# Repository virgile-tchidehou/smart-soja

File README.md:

<div align="center">

# 🌱 SMART-SOJA

### An Autonomous IoT-Based Mobile Soybean Pre-processing System

**[Documentation](#-documentation) · [Architecture](#️-system-architecture) · [Hardware](#️-hardware-overview) · [Roadmap](#-project-roadmap)**

</div>

---

SMART-SOJA is an academic engineering project co-developed by **Elisa Christelle LOKO** and **Dodji Virgile TCHIDEHOU**. It explores a mobile and connected soybean pre-processing unit designed to improve post-harvest handling in rural environments.

The prototype combines embedded systems, industrial automation, IoT technologies and an off-grid solar/battery architecture. At its current stage, the project is a **functional proof of concept**: the main sensing, actuation, drying and IoT subsystems have been validated individually or in partial integration, while full-cycle validation under a real 2–5 kg load and final HX711 weighing integration remain future work.

<div align="center">

</div>

---

## 📖 Table of Contents

- Overview
- The Problem
- Objectives
- Key Features
- System Architecture
- Hardware Overview
- Software Architecture
- Technology Stack
- Repository Structure
- Documentation
- Roadmap
- Future Improvements
- Project Team
- License

---

# 📌 Overview

Soybean production is rapidly increasing across Africa, particularly in Benin. However, post-harvest losses caused by inadequate cleaning, excessive moisture and poor traceability continue to reduce product quality and market value.

SMART-SOJA addresses these challenges by providing a mobile cyber-physical system capable of:

- Cleaning soybean grains through a vibrating sieve mechanism
- Measuring grain moisture at two points
- Controlling an active drying subsystem
- Supporting final batch weighing through an HX711-based subsystem *(final integration pending)*
- Recording production data locally
- Synchronizing traceability data through MQTT

The project integrates mechanical engineering, embedded electronics, industrial automation and cloud connectivity into a single modular platform.

---

# ❗ The Problem

Smallholder farmers often face several challenges:

- High post-harvest losses
- Non-uniform drying
- Manual quality control
- Lack of digital traceability
- Limited access to electricity

SMART-SOJA was designed to provide an affordable and intelligent solution adapted to rural environments.

---

# 🎯 Objectives

The project aims to:

- automate soybean pre-processing;
- improve grain quality before storage;
- reduce moisture-related losses;
- provide digital traceability;
- support off-grid operation through a solar/battery power architecture;
- support smart agriculture initiatives.

---

# ✨ Key Features

- 🌱 Mobile modular platform
- 📡 IoT connectivity using MQTT
- ⚙️ Embedded control with ESP32
- ☀️ Solar/battery off-grid power architecture
- 💧 Dual moisture sensing
- 🔥 Active drying control
- ⚖️ HX711-based weighing subsystem *(final integration pending)*
- 💾 Offline data logging (MicroSD)
- ☁️ Cloud synchronization
- 📊 Real-time monitoring
- 🧠 FreeRTOS multitasking architecture
- 🔄 GRAFCET-based sequential control

---

# 🏗️ System Architecture

SMART-SOJA is composed of six major subsystems:

## Mechanical System

- Modular chassis
- Cleaning mechanism
- Drying chamber
- Weighing module
- Mobile structure

## Embedded Electronics

- ESP32 microcontroller
- Sensors
- Power electronics
- Human-Machine Interface

## Energy System

- Solar panel
- Battery
- Charging controller
- DC converters

## Control System

- FreeRTOS scheduler
- GRAFCET automation
- Safety management

## IoT Layer

- MQTT communication
- JSON data exchange
- Cloud synchronization
- Store-and-Forward mechanism

## Traceability Layer

- Batch identification
- Local storage
- Cloud database
- Digital production records

---

# ⚙️ Hardware Overview

Main components include:

- ESP32 DevKit
- Capacitive moisture sensors
- HX711 load cell module
- Servo motors
- DC geared motors
- MOSFET power drivers
- LCD I2C display
- MicroSD module
- Solar panel
- Battery system

---

# 💻 Software Architecture

The embedded firmware is based on FreeRTOS.

Main software modules:

- Safety Task
- Control Task
- Sensor Task
- Actuator Task
- LCD Task
- MQTT Task

The control logic is modeled using a two-level GRAFCET to ensure deterministic and reliable operation.

---

# 🛠️ Technology Stack

## Embedded

- ESP32
- FreeRTOS
- Arduino IDE / Arduino Framework

## IoT

- MQTT (HiveMQ broker)
- JSON
- Wi-Fi

## Cloud & Web

- Node.js / Express (MQTT-to-cloud bridge API)
- Firebase (Firestore, Realtime Database, Hosting)
- Vite.js / Vanilla JavaScript (dashboard SPA)

## Mechanical

- SolidWorks

## Electronics

- KiCad

---

# 📁 Repository Structure

```text
smart-soja/
│
├── README.md                  # Présentation du projet
├── LICENSE
├── .gitignore
│
├── docs/                       # Documentation technique (9 chapitres + images)
│   ├── 01-project-overview.md
│   ├── 02-system-architecture.md
│   ├── 03-hardware-design.md
│   ├── 04-mechanical-design.md
│   ├── 05-software-architecture.md
│   ├── 06-energy-system.md
│   ├── 07-testing-validation.md
│   ├── 08-results.md
│   ├── 09-future-improvements.md
│   └── images/
│
├── firmware/
│   └── esp32/
│       └── src/                # Firmware ESP32 (FreeRTOS, GRAFCET)
│
├── hardware/                   # Conception électronique (KiCad)
│   ├── conception.md
│   ├── pcb/circuit_smart-soja/ # Projet KiCad complet (sch, pcb, gerbers, BOM)
│   ├── schematics/              # Exports PDF/SVG du schéma
│   ├── bom/                     # Nomenclature des composants
│   ├── wiring/                  # Schémas de brochage (pinout) des capteurs/modules
│   └── datasheets/               # Références vers les fiches techniques constructeur
│
├── mechanical/                 # Conception mécanique (SolidWorks)
│   ├── conception.md
│   ├── solidworks/
│   ├── stl/
│   ├── drawings/
│   └── renders/
│
├── cloud/
│   ├── mqtt/                   # Spécification du protocole ESP32 ↔ broker
│   ├── database/                # Documentation du schéma Firestore
│   ├── api/                     # Backend Node.js/Express (passerelle MQTT → Firebase)
│   └── dashboard/app/           # Plateforme web Vite.js (tableaux de bord)
│
├── media/                      # Photos du prototype, captures d'écran, diagrammes
│   ├── prototype/
│   ├── screenshots/
│   └── diagrams/
│
├── research/
│   └── thesis/                  # Mémoire complet (source de la documentation)
│
└── .github/
    └── ISSUE_TEMPLATE/
```

---

# 📚 Documentation

Full technical documentation lives in [`docs/`](docs/):

| Chapter | Content |
|---|---|
| [01 – Project Overview](docs/01-project-overview.md) | Context, problem statement, objectives |
| [02 – System Architecture](docs/02-system-architecture.md) | Edge / Cloud / Application layers |
| [03 – Hardware Design](docs/03-hardware-design.md) | ESP32, sensors, actuators, PCB |
| [04 – Mechanical Design](docs/04-mechanical-design.md) | Modular chassis and 4 functional blocks |
| [05 – Software Architecture](docs/05-software-architecture.md) | FreeRTOS, GRAFCET, MQTT/JSON, web dashboard |
| [06 – Energy System](docs/06-energy-system.md) | Solar/battery sizing |
| [07 – Testing & Validation](docs/07-testing-validation.md) | Unit test protocol and results |
| [08 – Results](docs/08-results.md) | Prototype outcomes, financial evaluation |
| [09 – Future Improvements](docs/09-future-improvements.md) | Validation roadmap and product evolution |

The technical documentation in this repository is derived from the academic thesis. The full thesis PDF is intentionally not distributed in the public repository; supporting figures and project material remain under [`research/thesis/`](research/thesis/).

---

# 🚀 Project Roadmap

- [x] Problem identification
- [x] Requirements analysis
- [x] Mechanical design
- [x] Electronic architecture
- [x] Embedded software
- [x] Prototype assembly and integration
- [x] Unit-level functional validation (sensors, actuators, MQTT traceability)

### Next Milestones

- [ ] Full clean + dry cycle validation under real load (2–5 kg)
- [ ] Load-cell (HX711) weighing module integration
- [ ] Field testing under real environmental conditions
- [ ] PCB redesign (multilayer)
- [ ] Mobile application
- [ ] OTA firmware updates
- [ ] AI-assisted moisture prediction
- [ ] Version 2 prototype

---

# 🌍 Future Vision

SMART-SOJA is envisioned as a scalable smart agriculture platform capable of supporting digital transformation in African agricultural value chains.

Future versions will integrate:

- Edge AI
- Predictive maintenance
- Computer vision
- Fleet management
- Remote diagnostics
- Industrial IoT deployment

---

<div align="center">

# 👥 Project Team

**Elisa Christelle LOKO** — Co-developer  
**Dodji Virgile TCHIDEHOU** — Co-developer · repository maintainer

Final-year project — Professional License in Industrial Computing & Maintenance, EGEI / UCAO-UUC, 2026.  
Academic supervisor: **Dr DIDAVI Audace**

This public repository is maintained by Dodji Virgile TCHIDEHOU and documents the team project together with the technical work contributed during its development.

</div>

---

# 📄 License

<div align="center">

This project is licensed under the [MIT License](LICENSE).

**🌱 SMART-SOJA — from the field to the factory, one certified batch at a time.**

</div>

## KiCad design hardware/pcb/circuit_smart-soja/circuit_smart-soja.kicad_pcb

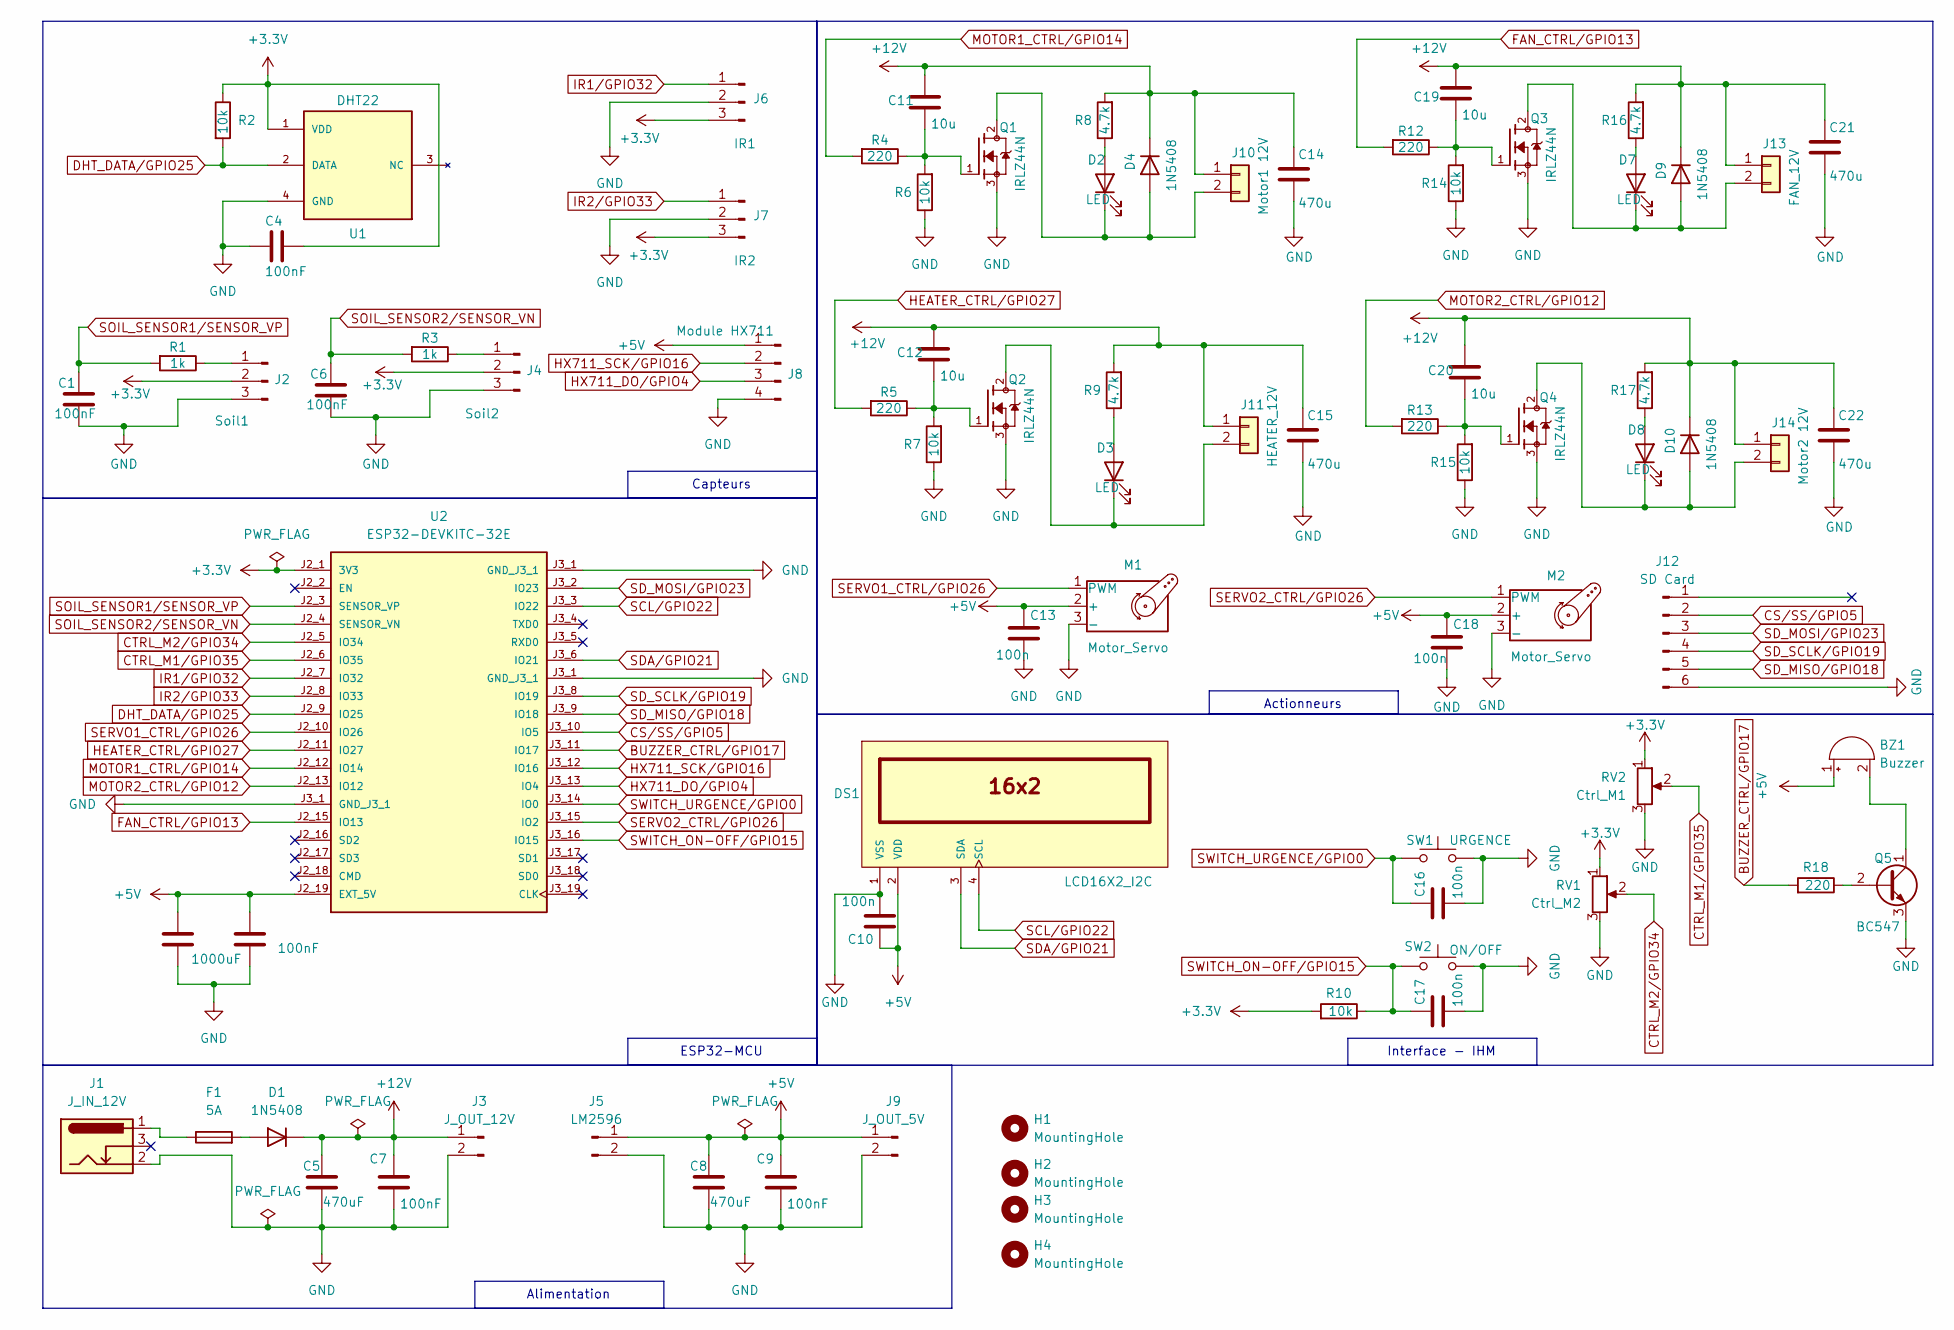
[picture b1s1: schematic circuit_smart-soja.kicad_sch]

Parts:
BZ1: Buzzer; Buzzer_12x9.5RM7.6
C1, C3, C4, C6, C7, C9: 100nF; C_Rect_L10.3mm_W4.5mm_P7.50mm_MKS4
C2: 1000uF; C_Radial_D8.0mm_H11.5mm_P3.50mm
C5, C8: 470uF; C_Radial_D10.0mm_H12.5mm_P5.00mm
C10, C13, C16, C17, C18: 100n; C_Rect_L10.3mm_W4.5mm_P7.50mm_MKS4
C11, C12, C19, C20: 10u; C_Radial_D8.0mm_H11.5mm_P3.50mm
C14, C15, C21, C22: 470u; C_Radial_D10.0mm_H12.5mm_P5.00mm
D1, D4, D9, D10: 1N5408; D_DO-201AD_P15.24mm_Horizontal
D2, D3, D7, D8: LED; LED_D3.0mm
DS1: LCD16X2_I2C; PinHeader_1x04_P2.54mm_Vertical
F1: 5A; Fuse_SunFuse-6HP
H1, H2, H3, H4: MountingHole; MountingHole_3.2mm_M3
J1: J_IN_12V; BarrelJack_Horizontal
J2: Soil1; PinHeader_1x03_P2.54mm_Vertical
J3: J_OUT_12V; TerminalBlock_Phoenix_MKDS-1,5-2-5.08_1x02_P5.08mm_Horizont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
J4: Soil2; PinHeader_1x03_P2.54mm_Vertical
J5: LM2596; TerminalBlock_Phoenix_MKDS-1,5-2-5.08_1x02_P5.08mm_Horizont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
J6: IR1; PinHeader_1x03_P2.54mm_Vertical
J7: IR2; PinHeader_1x03_P2.54mm_Vertical
J8: Module HX711; PinHeader_1x04_P2.54mm_Vertical
J9: J_OUT_5V; TerminalBlock_Phoenix_MKDS-1,5-2-5.08_1x02_P5.08mm_Horizont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
J10: Motor1 12V; TerminalBlock_Phoenix_MKDS-1,5-2-5.08_1x02_P5.08mm_Horizont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
J11: HEATER_12V; TerminalBlock_Phoenix_MKDS-1,5-2-5.08_1x02_P5.08mm_Horizont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
J12: SD Card; PinHeader_1x06_P2.54mm_Vertical
J13: FAN_12V; TerminalBlock_Phoenix_MKDS-1,5-2-5.08_1x02_P5.08mm_Horizont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
J14: Motor2 12V; TerminalBlock_Phoenix_MKDS-1,5-2-5.08_1x02_P5.08mm_Horizont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
M1, M2: Motor_Servo; PinHeader_1x03_P2.54mm_Vertical
Q1, Q2, Q3, Q4: IRLZ44N; TO-220-3_Vertical; PARTREV 11/11/03
Q5: BC547; TO-92L_HandSolder
R1, R3: 1k; R_Axial_DIN0414_L11.9mm_D4.5mm_P20.32mm_Horizontal
R2, R6, R7, R10, R14, R15: 10k; R_Axial_DIN0414_L11.9mm_D4.5mm_P20.32mm_Horizontal
R4, R5, R12, R13, R18: 220; R_Axial_DIN0414_L11.9mm_D4.5mm_P20.32mm_Horizontal
R8, R9, R16, R17: 4.7k; R_Axial_DIN0414_L11.9mm_D4.5mm_P20.32mm_Horizontal
RV1: Ctrl_M2; Potentiometer_Alps_RK163_Single_Horizontal
RV2: Ctrl_M1; Potentiometer_Alps_RK163_Single_Horizontal
SW1: URGENCE; SW_PUSH_6mm_H4.3mm
SW2: ON/OFF; SW_PUSH_6mm_H4.3mm
U1: DHT22; PinHeader_1x04_P2.54mm_Vertical
U2: ESP32-DEVKITC-32E; MODULE_ESP32-DEVKITC-32E; PARTREV 1.4

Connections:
+3.3V: C4.1, J2.2, J4.2, J6.3, J7.3, R2.1, R10.2, RV1.1, RV2.1, U1.1 (VDD), U2.J2_1 (3V3)
+5V: BZ1.1 (+), C2.1, C3.1, C8.1, C9.1, C10.1, C13.1, C18.1, DS1.2 (VDD), J5.1, J8.1, J9.1, M1.2 (+), M2.2 (+), U2.J2_19 (EXT_5V)
+12V: C5.1, C7.1, C11.1, C12.1, C14.1, C15.1, C19.1, C20.1, C21.1, C22.1, D1.1 (K), D4.1 (K), D9.1 (K), D10.1 (K), J3.1, J10.1, J11.1, J13.1, J14.1, R8.2, R9.2, R16.2, R17.2
BUZZER_CTRL/GPIO17: R18.2, U2.J3_11 (IO17)
CS/SS/GPIO5: J12.2, U2.J3_10 (IO5)
CTRL_M1/GPIO35: RV2.2, U2.J2_6 (IO35)
CTRL_M2/GPIO34: RV1.2, U2.J2_5 (IO34)
DHT_DATA/GPIO25: R2.2, U1.2 (DATA), U2.J2_9 (IO25)
FAN_CTRL/GPIO13: R12.2, U2.J2_15 (IO13)
GND: C1.2, C2.2, C3.2, C4.2, C5.2, C6.2, C7.2, C8.2, C9.2, C10.2, C13.2, C14.2, C15.2, C16.2, C17.2, C18.2, C21.2, C22.2, DS1.1 (VSS), J1.2, J2.3, J3.2, J4.3, J5.2, J6.2, J7.2, J8.4, J9.2, J12.6, M1.3 (-), M2.3 (-), Q1.3, Q2.3, Q3.3, Q4.3, Q5.3 (E), R6.1, R7.1, R14.1, R15.1, RV1.3, RV2.3, SW1.2, SW2.2, U1.4 (GND), U2.J3_1 (GND_J3_1)
HEATER_CTRL/GPIO27: R5.2, U2.J2_11 (IO27)
HX711_DO/GPIO4: J8.3, U2.J3_13 (IO4)
HX711_SCK/GPIO16: J8.2, U2.J3_12 (IO16)
IR1/GPIO32: J6.1, U2.J2_7 (IO32)
IR2/GPIO33: J7.1, U2.J2_8 (IO33)
MOTOR1_CTRL/GPIO14: R4.2, U2.J2_12 (IO14)
MOTOR2_CTRL/GPIO12: R13.2, U2.J2_13 (IO12)
unnamed: BZ1.2 (-), Q5.1 (C)
unnamed: C11.2, Q1.1, R4.1, R6.2
unnamed: C12.2, Q2.1, R5.1, R7.2
unnamed: C19.2, Q3.1, R12.1, R14.2
unnamed: C20.2, Q4.1, R13.1, R15.2
unnamed: D1.2 (A), F1.2
unnamed: D2.2 (A), R8.1
unnamed: D2.1 (K), D4.2 (A), J10.2, Q1.2
unnamed: D3.2 (A), R9.1
unnamed: D3.1 (K), J11.2, Q2.2
unnamed: D7.2 (A), R16.1
unnamed: D7.1 (K), D9.2 (A), J13.2, Q3.2
unnamed: D8.2 (A), R17.1
unnamed: D8.1 (K), D10.2 (A), J14.2, Q4.2
unnamed: F1.1, J1.1
unnamed: J2.1, R1.1
unnamed: J4.1, R3.1
unnamed: Q5.2 (B), R18.1
SCL/GPIO22: DS1.4 (SCL), U2.J3_3 (IO22)
SDA/GPIO21: DS1.3 (SDA), U2.J3_6 (IO21)
SD_MISO/GPIO18: J12.5, U2.J3_9 (IO18)
SD_MOSI/GPIO23: J12.3, U2.J3_2 (IO23)
SD_SCLK/GPIO19: J12.4, U2.J3_8 (IO19)
SERVO1_CTRL/GPIO26: M1.1 (PWM), U2.J2_10 (IO26)
SERVO2_CTRL/GPIO26: M2.1 (PWM), U2.J3_15 (IO2)
SOIL_SENSOR1/SENSOR_VP: C1.1, R1.2, U2.J2_3 (SENSOR_VP)
SOIL_SENSOR2/SENSOR_VN: C6.1, R3.2, U2.J2_4 (SENSOR_VN)
SWITCH_ON-OFF/GPIO15: C17.1, R10.1, SW2.1, U2.J3_16 (IO15)
SWITCH_URGENCE/GPIO0: C16.1, SW1.1, U2.J3_14 (IO0)

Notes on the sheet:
Interface - IHM
ESP32-MCU
Alimentation
Actionneurs
Capteurs

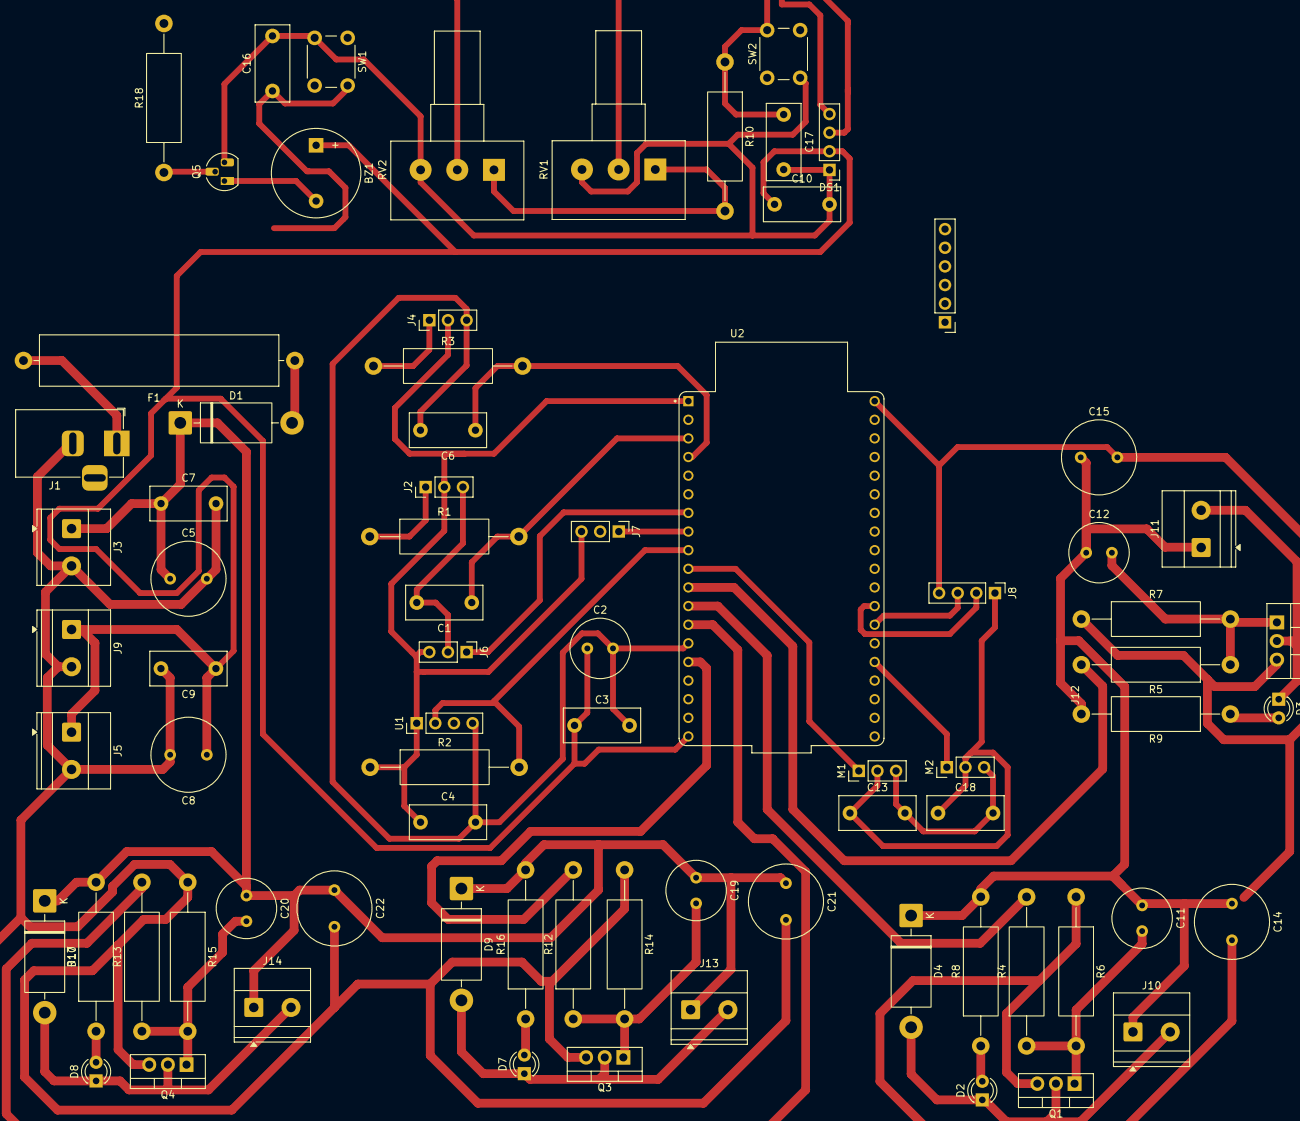
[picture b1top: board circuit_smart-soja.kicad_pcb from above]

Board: 2 copper layers, 81 parts (0 on the bottom side), 46 nets.

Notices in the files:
README.md:
License: MIT
